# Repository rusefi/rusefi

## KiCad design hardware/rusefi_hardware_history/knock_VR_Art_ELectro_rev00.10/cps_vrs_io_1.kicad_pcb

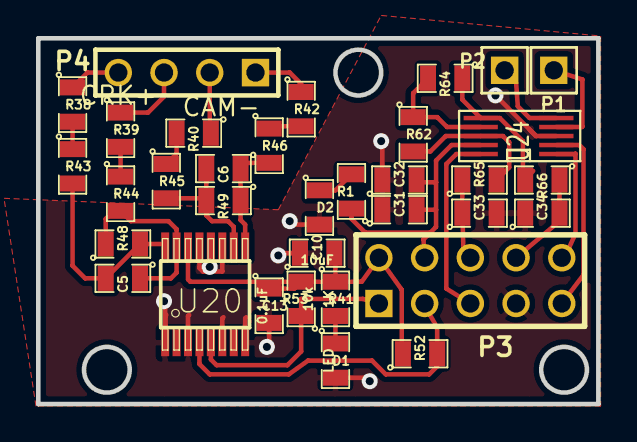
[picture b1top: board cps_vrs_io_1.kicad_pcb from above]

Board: 2 copper layers, 31.1 x 20.3 mm, 35 parts (1 on the bottom side), 29 nets.

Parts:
C5, C6, C34: 1000pF; SM0805
C10: 10uF; SM0805
C13, C32, C33: 0.1uF; SM0805
C31: 1uF; SM0805
D1, D2: LED; SM0805
G1: LOGO; LOGO_F
P1, P2: CONN_1; PIN_ARRAY_1
P3: CONN_5X2; PIN_ARRAY_5x2
P4: CONN_4; PIN_ARRAY_4x1
R1, R41: 1K; SM0805
R38, R39, R40, R42, R43, R44, R45, R46, R48, R49: 5k; SM0805
R52, R53: 10k; SM0805
R62, R64: 10K; SM0805
R65, R66: 20K; SM0805
U20: MAX9926/9927; maxim-10-QSOP16
U24: MAX9939; uMAX-uSOP_10

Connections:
/5V: C10.2, C13.1, P3.2, R41.1, R52.1, R53.2, U20.14
/5v stab: C31.2, C32.2, P3.4, R1.1, U24.9
/CAM: P3.1, R53.1, U20.5
/CAM+: P4.1, R42.1
/CAM-: P4.2, R40.1
/CRANK: P3.3, R52.2, U20.4
/CRK2+: P4.4, R38.1
/CRK2-: P4.3, R39.1
/CS-KN1: P3.5, U24.10
/MISO: P3.9, U24.2
/SCK: P3.10, U24.1
/knock1+: C33.1, P3.6, R65.1
/knock1-: C34.2, P3.8, R66.1
/knock_1+p: P2.1, U24.5
/knock_1-p: P1.1, U24.4
GND: C10.1, C13.2, C31.1, C32.1, C33.2, C34.1, D1.2, D2.2, P3.7, U20.1, U20.3, U20.6, U20.8, U20.11, U20.12, U20.13, U24.3
unnamed: R62.1, R64.2, U24.7
unnamed: R62.2, R65.2, U24.8
unnamed: R64.1, R66.2, U24.6
unnamed: D1.1, R41.2
unnamed: D2.1, R1.2
unnamed: R38.2, R43.1
unnamed: R40.2, R45.1
unnamed: R42.2, R46.1
unnamed: R39.2, R44.1
unnamed: C5.1, R44.2, R48.1, U20.15
unnamed: C5.2, R43.2, R48.2, U20.16
unnamed: C6.1, R46.2, R49.1, U20.9
unnamed: C6.2, R45.2, R49.2, U20.10

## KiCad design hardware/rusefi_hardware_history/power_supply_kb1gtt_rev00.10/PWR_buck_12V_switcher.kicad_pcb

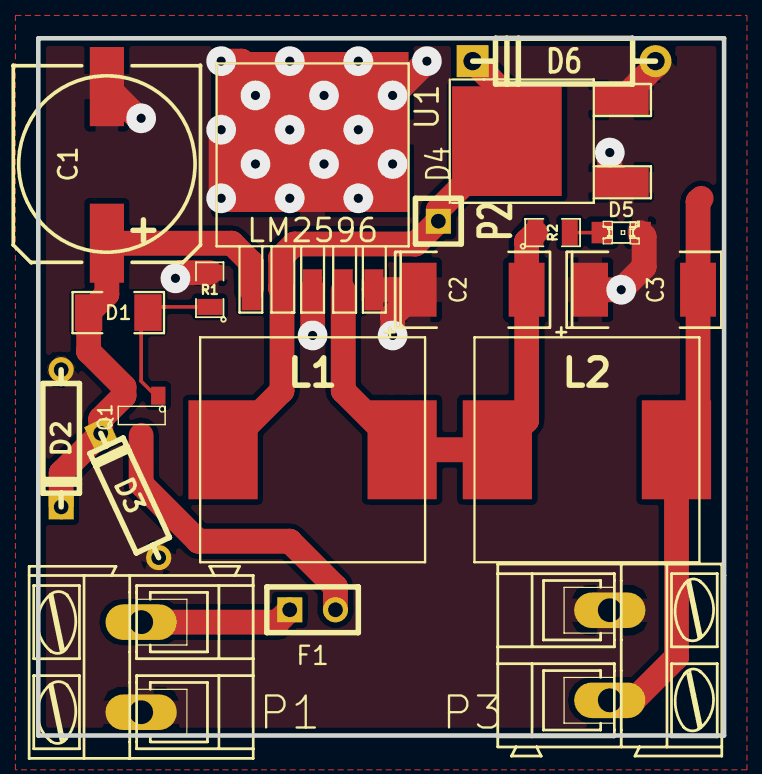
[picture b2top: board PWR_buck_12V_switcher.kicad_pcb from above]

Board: 2 copper layers, 38.1 x 38.7 mm, 19 parts (0 on the bottom side), 9 nets.

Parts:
C1: 470uF 25V; SMDSVP10
C2, C3: 220uF; SM2512
D1: ZENERSMALL; SM1206
D2, D3: TVS; D3
D4: SCHDPAK; DPAK2
D5: GREEN; LED-0805
D6: DIODESCH; D4
F1: 3.5A; SIL-2
L1, L2: 38uH; SM100uH
P1, P3: CONN_2; AK300-2
P2: CONN_1; SIL-1
Q1: MOS_PRO; SOT23
R1, R2: 1k; SM0805
U1: LM2596; DPAK5

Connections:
/5V-REG: C3.2, L2.2, P3.2
/FB: C2.2, L1.2, L2.1, R2.1, U1.4
/OUT: D4.2, D6.2, L1.1, P2.1, U1.2
/VBAT: C1.1, D1.2, D2.2, D3.2, Q1.2, U1.1
/Vf: F1.2, Q1.3
/Vin: F1.1, P1.2
GND: C1.2, C2.1, C3.1, D2.1, D3.1, D4.1, D4.3, D5.2, D6.1, P1.1, P3.1, R1.2, U1.3, U1.5
unnamed: D1.1, Q1.1, R1.1
unnamed: D5.1, R2.2

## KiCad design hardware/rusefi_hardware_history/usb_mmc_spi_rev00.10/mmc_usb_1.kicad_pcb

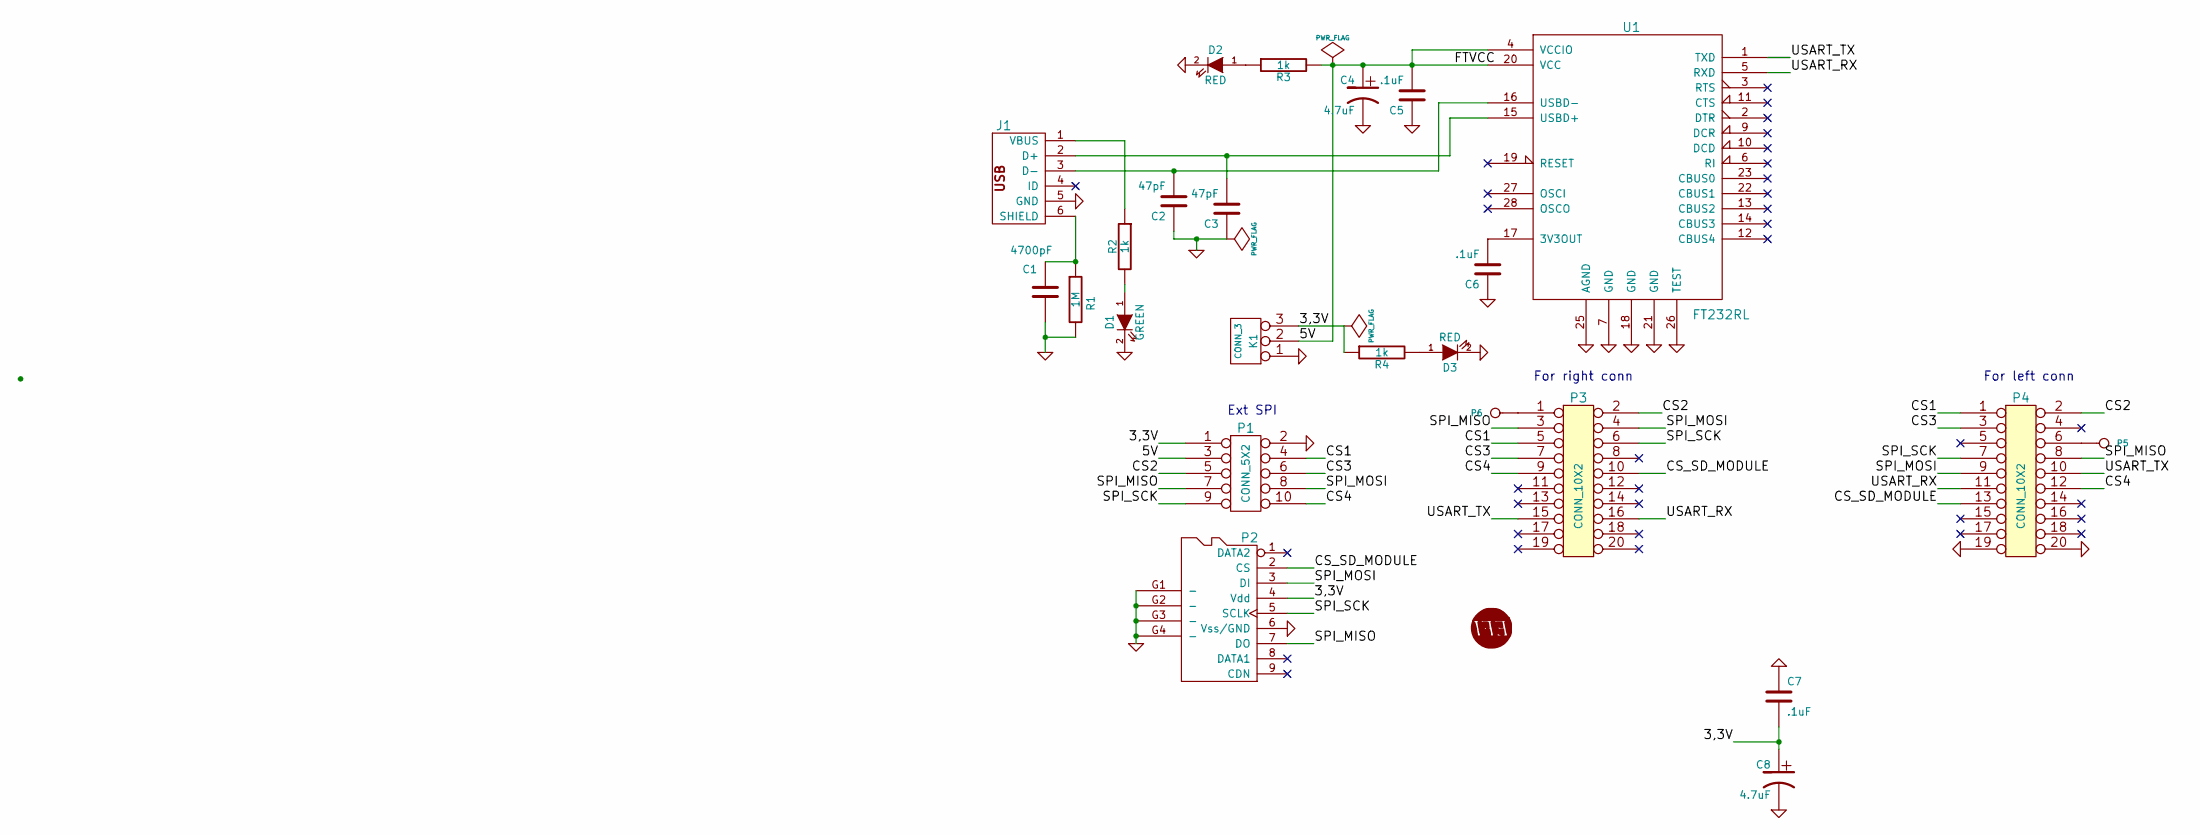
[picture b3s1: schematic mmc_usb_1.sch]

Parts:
C1: 4700pF
C2, C3: 47pF
C4, C8: 4.7uF
C5, C6, C7: .1uF
D1: GREEN
D2, D3: RED
G1: LOGO
J1: MINI-USB-5P-3400020P1
K1: CONN_3
P1: CONN_5X2
P2: MICRO-SDCARD-CONNECTOR-3300060P1
P3, P4: CONN_10X2
P5, P6: CONN_1
R1: 1M
R2, R3, R4: 1k
U1: FT232RL

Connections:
/3,3V: C7.2, C8.1, K1.3, P1.1, P2.4 (Vdd), R4.1
/5V: C4.1, C5.2, K1.2 (PM), P1.3, R3.2, U1.4 (VCCIO), U1.20 (VCC)
/CS1: P1.4, P3.5, P4.1
/CS2: P1.5, P3.2, P4.2
/CS3: P1.6, P3.7, P4.3
/CS4: P1.10, P3.9, P4.12
/CS_SD_MODULE: P2.2 (CS), P3.10, P4.13
/SPI_MISO: P1.7, P2.7 (DO), P3.3, P4.8
/SPI_MOSI: P1.8, P2.3 (DI), P3.4, P4.9
/SPI_SCK: P1.9, P2.5 (SCLK), P3.6, P4.7
/USART_RX: P3.16, P4.11, U1.5 (RXD)
/USART_TX: P3.15, P4.10, U1.1 (TXD)
GND: C1.1, C2.1, C3.1, C4.2, C5.1, C6.1, C7.1, C8.2, D1.2 (K), D2.2 (K), D3.2 (K), J1.5 (GND), K1.1, P1.2, P2.6 (Vss/GND), P2.G1 (-), P2.G2 (-), P2.G3 (-), P2.G4 (-), P4.19, P4.20, R1.2, U1.7 (GND), U1.18 (GND), U1.21 (GND), U1.25 (AGND), U1.26 (TEST)
unnamed: C1.2, J1.6 (SHIELD), R1.1
unnamed: J1.1 (VBUS), R2.1
unnamed: C3.2, J1.2 (D+), U1.15 (USBD+)
unnamed: D1.1 (A), R2.2
unnamed: P4.6, P5.1
unnamed: P3.1, P6.1
unnamed: C6.2, U1.17 (3V3OUT)
unnamed: D2.1 (A), R3.1
unnamed: C2.2, J1.3 (D-), U1.16 (USBD-)
unnamed: D3.1 (A), R4.2

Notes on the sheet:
Ext SPI
For left conn
For right conn

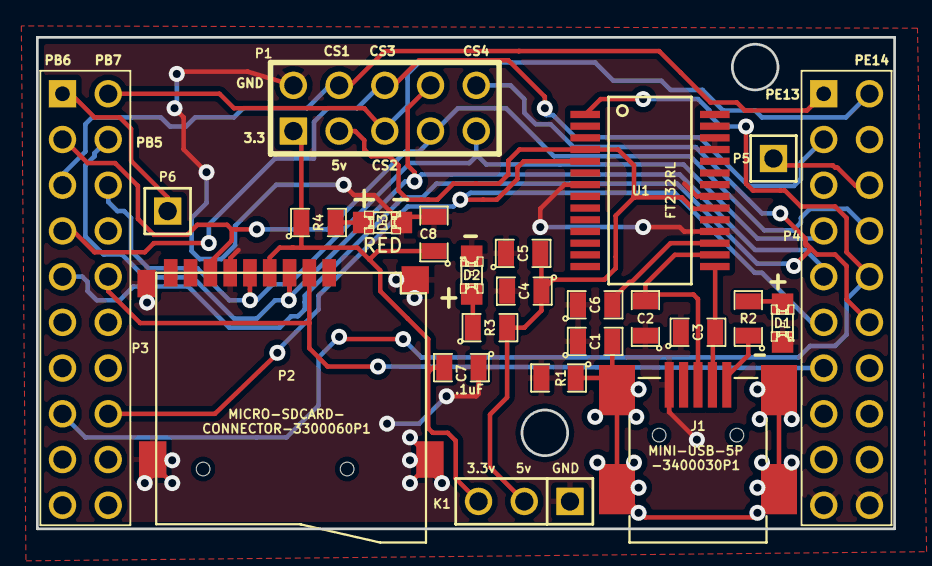
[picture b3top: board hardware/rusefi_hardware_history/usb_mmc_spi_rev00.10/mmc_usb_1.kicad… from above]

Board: 2 copper layers, 47.6 x 27.3 mm, 25 parts (1 on the bottom side), 23 nets.

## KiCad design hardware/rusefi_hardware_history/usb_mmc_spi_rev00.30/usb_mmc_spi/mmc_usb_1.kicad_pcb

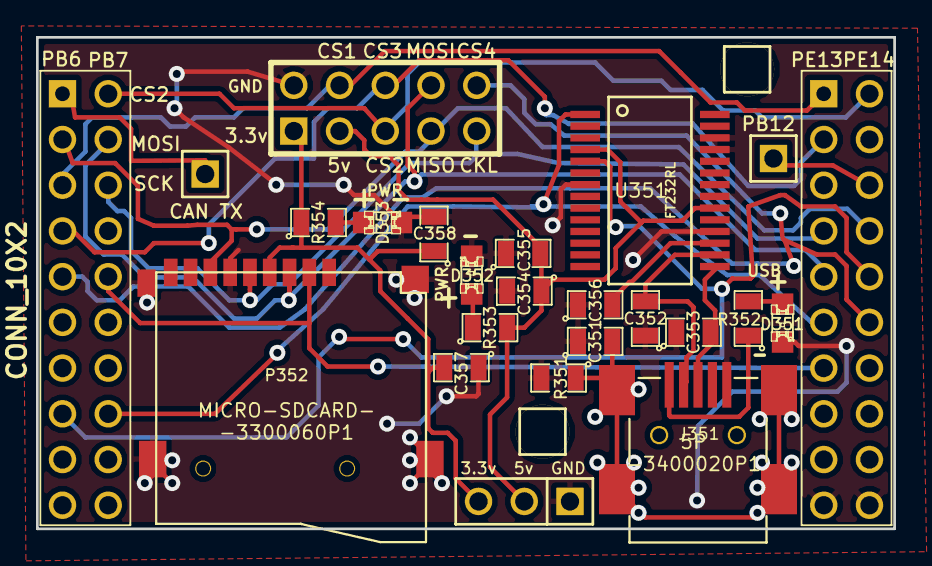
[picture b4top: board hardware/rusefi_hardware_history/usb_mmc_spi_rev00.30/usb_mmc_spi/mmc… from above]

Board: 2 copper layers, 47.6 x 27.3 mm, 27 parts (1 on the bottom side), 23 nets.

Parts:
C351: 4700pF; SM0805
C352, C353: 47pF; SM0805
C354, C358: 4.7uF; SM0805
C355, C356, C357: .1uF; SM0805
D351: GREEN; LED-0805_A
D352, D353: RED; LED-0805_A
G305: LOGO; LOGO_F
J351: MINI-USB-5P-3400020P1
K351: CONN_3; PIN_ARRAY_3_A
M351, M352: CONN_1; PIN_ARRAY_1
P351: CONN_5X2; PIN_ARRAY_5x2_M
P352: MICRO-SDCARD-CONNECTOR-3300060P1
P353, P354: CONN_10X2; PIN_ARRAY_10X2_M
P355, P356: CONN_1; PIN_ARRAY_1
R351: 1M; SM0805
R352, R353, R354: 1k; SM0805
U351: FT232RL; ssop-28

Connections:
/3.3V: C357.2, C358.1, K351.3, P351.1, P352.4, R354.1
/5V: C354.1, C355.2, K351.2, P351.3, R353.2, U351.4, U351.20
/CAN_TX: P353.1, P356.1
/CS1: P351.4, P353.5, P354.1
/CS2: P351.5, P353.2, P354.2
/CS3: P351.6, P353.7, P354.3
/CS4: P351.10, P353.9, P354.12
/CS_SD_MODULE: P352.2, P353.10, P354.13
/D+: C353.2, J351.3, U351.15
/D-: C352.2, J351.2, U351.16
/SPI_MISO: P351.7, P352.7, P353.3, P354.8
/SPI_MOSI: P351.8, P352.3, P353.4, P354.9
/SPI_SCK: P351.9, P352.5, P353.6, P354.7
/USART_RX: P353.16, P354.11, U351.1
/USART_TX: P353.15, P354.10, U351.5
GND: C351.1, C352.1, C353.1, C354.2, C355.1, C356.1, C357.1, C358.2, D351.2, D352.2, D353.2, J351.5, K351.1, P351.2, P352.6, P352.G1, P352.G2, P352.G3, P352.G4, P354.19, P354.20, R351.2, U351.7, U351.18, U351.21, U351.25, U351.26
unnamed: J351.1, R352.1
unnamed: C351.2, J351.6, R351.1
unnamed: D351.1, R352.2
unnamed: D353.1, R354.2
unnamed: D352.1, R353.1
unnamed: P354.6, P355.1
unnamed: C356.2, U351.17

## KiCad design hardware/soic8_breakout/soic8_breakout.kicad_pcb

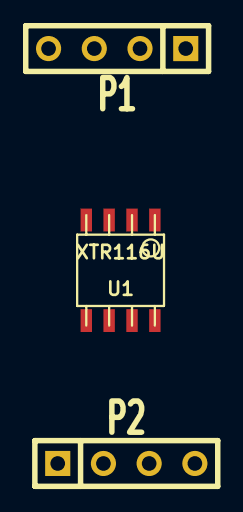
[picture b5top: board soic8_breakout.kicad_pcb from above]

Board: 2 copper layers, 3 parts (0 on the bottom side), 4 nets, no tracks yet.

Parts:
P1, P2: CONN_4; SIL-4
U1: XTR116U; so-8

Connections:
unnamed: P2.2, U1.6
unnamed: P1.3, U1.3
unnamed: P1.2, U1.2
unnamed: P1.1, U1.1

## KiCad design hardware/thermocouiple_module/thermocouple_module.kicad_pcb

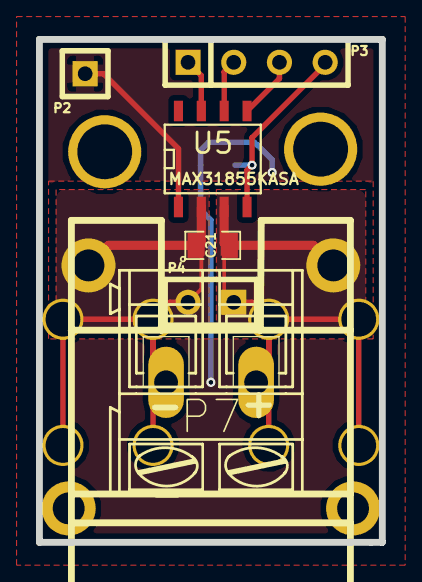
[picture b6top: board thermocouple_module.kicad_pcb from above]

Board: 2 copper layers, 19.0 x 27.9 mm, 12 parts (1 on the bottom side), 7 nets.

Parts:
C8: 100nF; SM0805-SM0603
C21: 10nF; SM0805-SM0603
P1: CONN_2; tcpl_PCC-SMP
P2: CONN_1; SIL-1
P3: CONN_4; SIL-4
P4: CONN_2; SIL-2
P5, P6: CONN_1; SCREW_TERM_534-7693
P7: CONN_2; AK300-2
U5: MAX31855KASA; SO8E
V801, V802: VIA; 1pin

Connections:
3.3v: C8.1, P3.4, U5.4
//CS: P3.2, U5.6
/MISO: P3.1, U5.7
/SCK: P3.3, U5.5
/TCPL+: C21.2, P1.2, P4.1, P6.1, P7.1, U5.3
/TCPL-: C21.1, P1.1, P4.2, P5.1, P7.2, U5.2
GND: C8.2, P2.1, U5.1
